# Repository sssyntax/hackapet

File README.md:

# Hackapet

A YSWS where you code + design a virtual pet, and we ship you a physical hackable tamagotchi clone to play it on!

Check out the site: https://hackapet.hackclub.com - includes more info + getting started guide!

## on submissions

When you've finished your game, create a PR in the /pets folder! 

Call your PR whatever your pet/game is named - also, **put your slack username in the PR comment so I can find you**!!

Note:
- you must be in high school (or younger!)
- all art must be drawn by you
- try to have at least 2 minutes of gameplay
- also: try to add on something more than what the example has

This YSWS ends Fed 3rd - get your pets in before then :D

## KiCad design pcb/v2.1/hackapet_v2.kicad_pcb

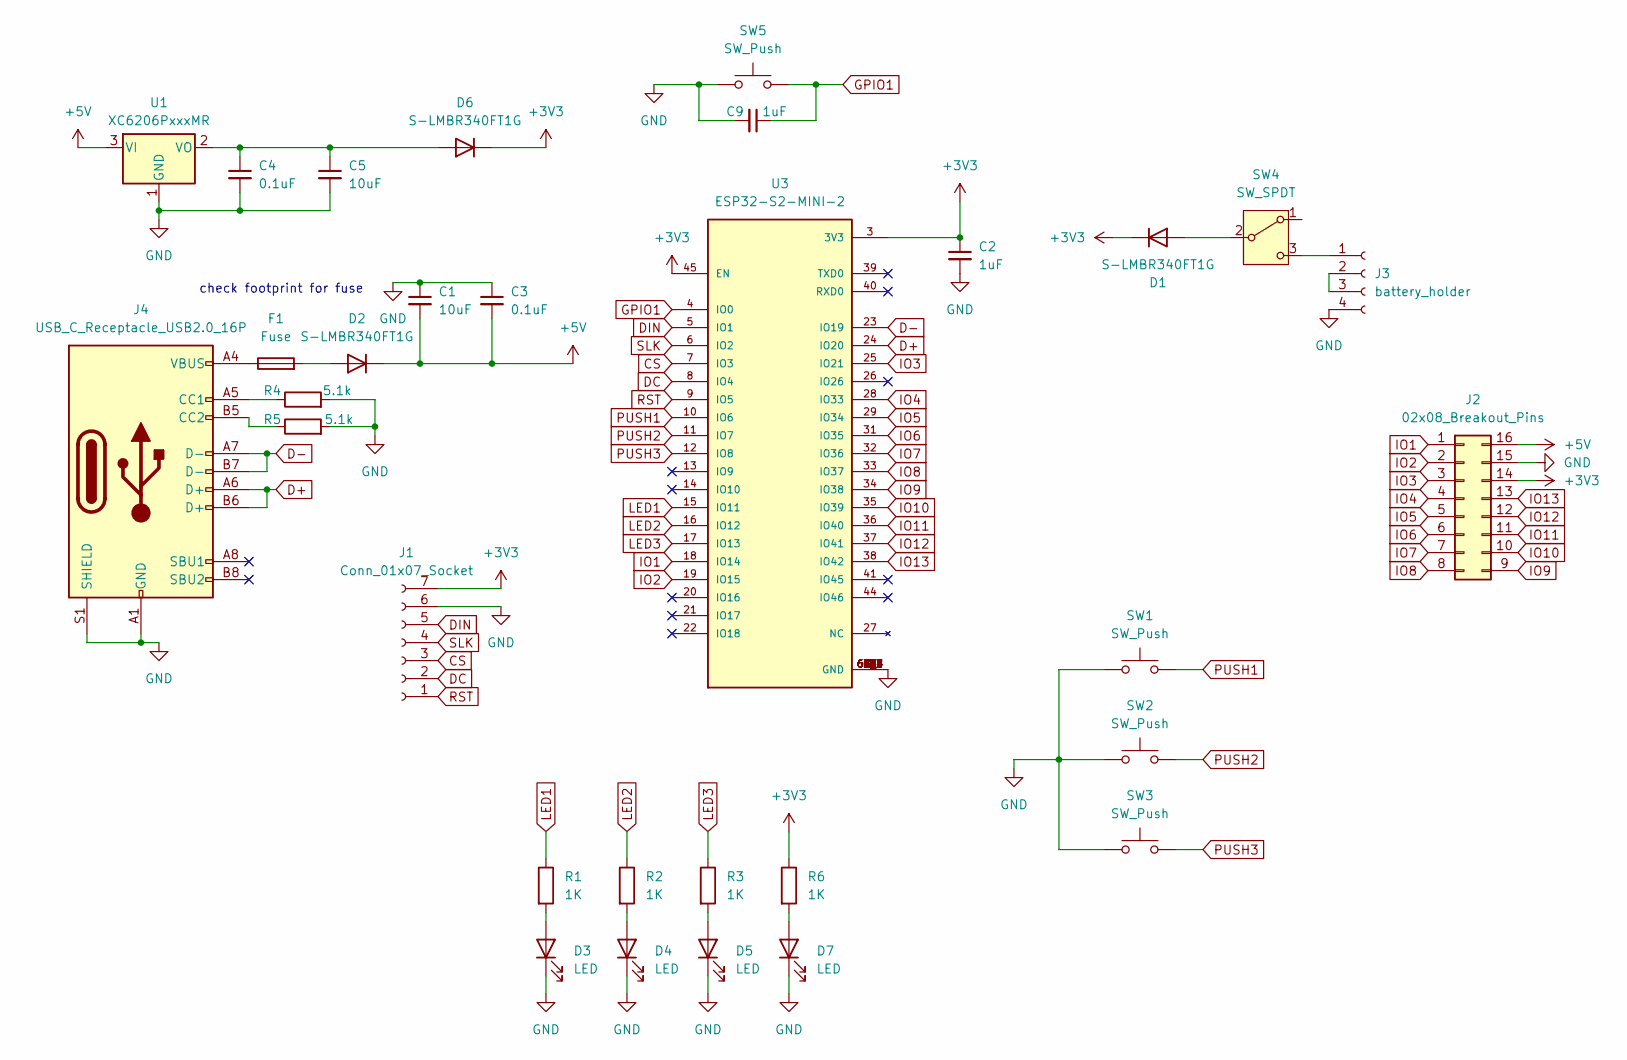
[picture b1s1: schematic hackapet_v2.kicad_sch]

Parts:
C1, C5: 10uF; C_0805_2012Metric; LCSC C5189822
C2, C9: 1uF; C_0805_2012Metric; LCSC C215803
C3, C4: 0.1uF; C_0805_2012Metric; LCSC C28378
D1, D2, D6: S-LMBR340FT1G; D_0805_2012Metric; LCSC C2972823
D3, D4, D5, D7: LED; LED_0805_2012Metric
F1: Fuse; Fuse_Bourns_MF-RHT050
J1: Conn_01x07_Socket; PinSocket_1x07_P2.54mm_Vertical; LCSC C22438073
J2: 02x08_Breakout_Pins; PinSocket_2x08_P2.54mm_Vertical; LCSC C30734
J3: battery_holder; 1022_batteryholder
J4: USB_C_Receptacle_USB2.0_16P; USB_C_Receptacle_HCTL_HC-TYPE-C-16P-01A; LCSC C393939
R1, R2, R3, R6: 1K; R_0805_2012Metric; LCSC C17513
R4, R5: 5.1k; R_0805_2012Metric; LCSC C104375
SW1, SW2, SW3, SW5: SW_Push; SW_Push_1P1T_NO_6x6mm_H9.5mm; LCSC C381038
SW4: SW_SPDT; SW_DPDT_CK_JS202011JCQN; LCSC C221666
U1: XC6206PxxxMR; SOT-23-3
U3: ESP32-S2-MINI-2; XCVR_ESP32-S2-MINI-1; PARTREV 1.0; LCSC C3013906

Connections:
+3V3: C2.1, D1.1 (K), D6.1 (K), J1.7, J2.14, R6.1, U3.3 (3V3), U3.45 (EN)
+5V: C1.2, C3.2, D2.1 (K), J2.16, U1.3 (VI)
CS: J1.3, U3.7 (IO3)
D+: J4.A6 (D+), J4.B6 (D+), U3.24 (IO20)
D-: J4.A7 (D-), J4.B7 (D-), U3.23 (IO19)
DC: J1.2, U3.8 (IO4)
DIN: J1.5, U3.5 (IO1)
GND: C1.1, C2.2, C3.1, C4.2, C5.2, C9.2, D3.1 (K), D4.1 (K), D5.1 (K), D7.1 (K), J1.6, J2.15, J3.4, J4.A1 (GND), J4.A12 (GND), J4.B1 (GND), J4.B12 (GND), J4.S1 (SHIELD), R4.2, R5.2, SW1.1, SW2.1, SW3.1, SW5.1, U1.1 (GND), U3.1 (GND), U3.2 (GND), U3.30 (GND), U3.42 (GND), U3.43 (GND), U3.46 (GND), U3.47 (GND), U3.48 (GND), U3.49 (GND), U3.50 (GND), U3.51 (GND), U3.52 (GND), U3.53 (GND), U3.54 (GND), U3.55 (GND), U3.56 (GND), U3.57 (GND), U3.58 (GND), U3.59 (GND), U3.60 (GND), U3.61 (GND), U3.61_1 (GND), U3.61_2 (GND), U3.61_3 (GND), U3.61_4 (GND), U3.61_5 (GND), U3.61_6 (GND), U3.61_7 (GND), U3.61_8 (GND), U3.62 (GND), U3.63 (GND), U3.64 (GND), U3.65 (GND)
GPIO1: C9.1, SW5.2, U3.4 (IO0)
IO1: J2.1, U3.18 (IO14)
IO2: J2.2, U3.19 (IO15)
IO3: J2.3, U3.25 (IO21)
IO4: J2.4, U3.28 (IO33)
IO5: J2.5, U3.29 (IO34)
IO6: J2.6, U3.31 (IO35)
IO7: J2.7, U3.32 (IO36)
IO8: J2.8, U3.33 (IO37)
IO9: J2.9, U3.34 (IO38)
IO10: J2.10, U3.35 (IO39)
IO11: J2.11, U3.36 (IO40)
IO12: J2.12, U3.37 (IO41)
IO13: J2.13, U3.38 (IO42)
LED1: R1.1, U3.15 (IO11)
LED2: R2.1, U3.16 (IO12)
LED3: R3.1, U3.17 (IO13)
unnamed: D1.2 (A), SW4.2 (B)
unnamed: D2.2 (A), F1.2
unnamed: D3.2 (A), R1.2
unnamed: D4.2 (A), R2.2
unnamed: D5.2 (A), R3.2
unnamed: C4.1, C5.1, D6.2 (A), U1.2 (VO)
unnamed: D7.2 (A), R6.2
unnamed: F1.1, J4.A4 (VBUS), J4.A9 (VBUS), J4.B4 (VBUS), J4.B9 (VBUS)
unnamed: J3.1, SW4.3 (C)
unnamed: J3.2, J3.3
unnamed: J4.A5 (CC1), R4.1
unnamed: J4.B5 (CC2), R5.1
PUSH1: SW1.2, U3.10 (IO6)
PUSH2: SW2.2, U3.11 (IO7)
PUSH3: SW3.2, U3.12 (IO8)
RST: J1.1, U3.9 (IO5)
SLK: J1.4, U3.6 (IO2)

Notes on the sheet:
check footprint for fuse

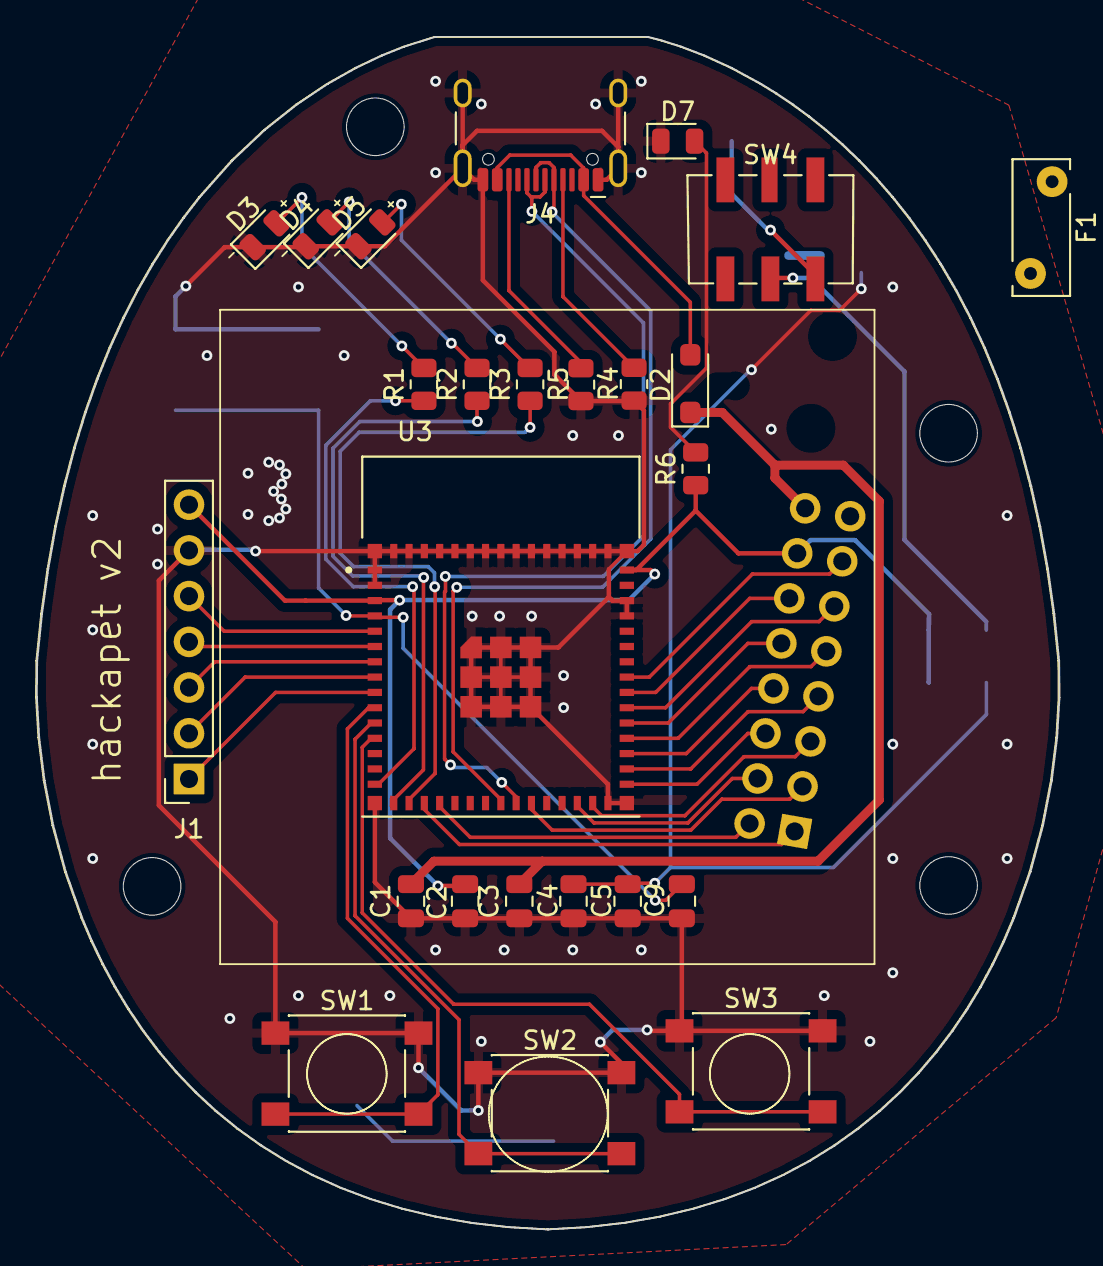
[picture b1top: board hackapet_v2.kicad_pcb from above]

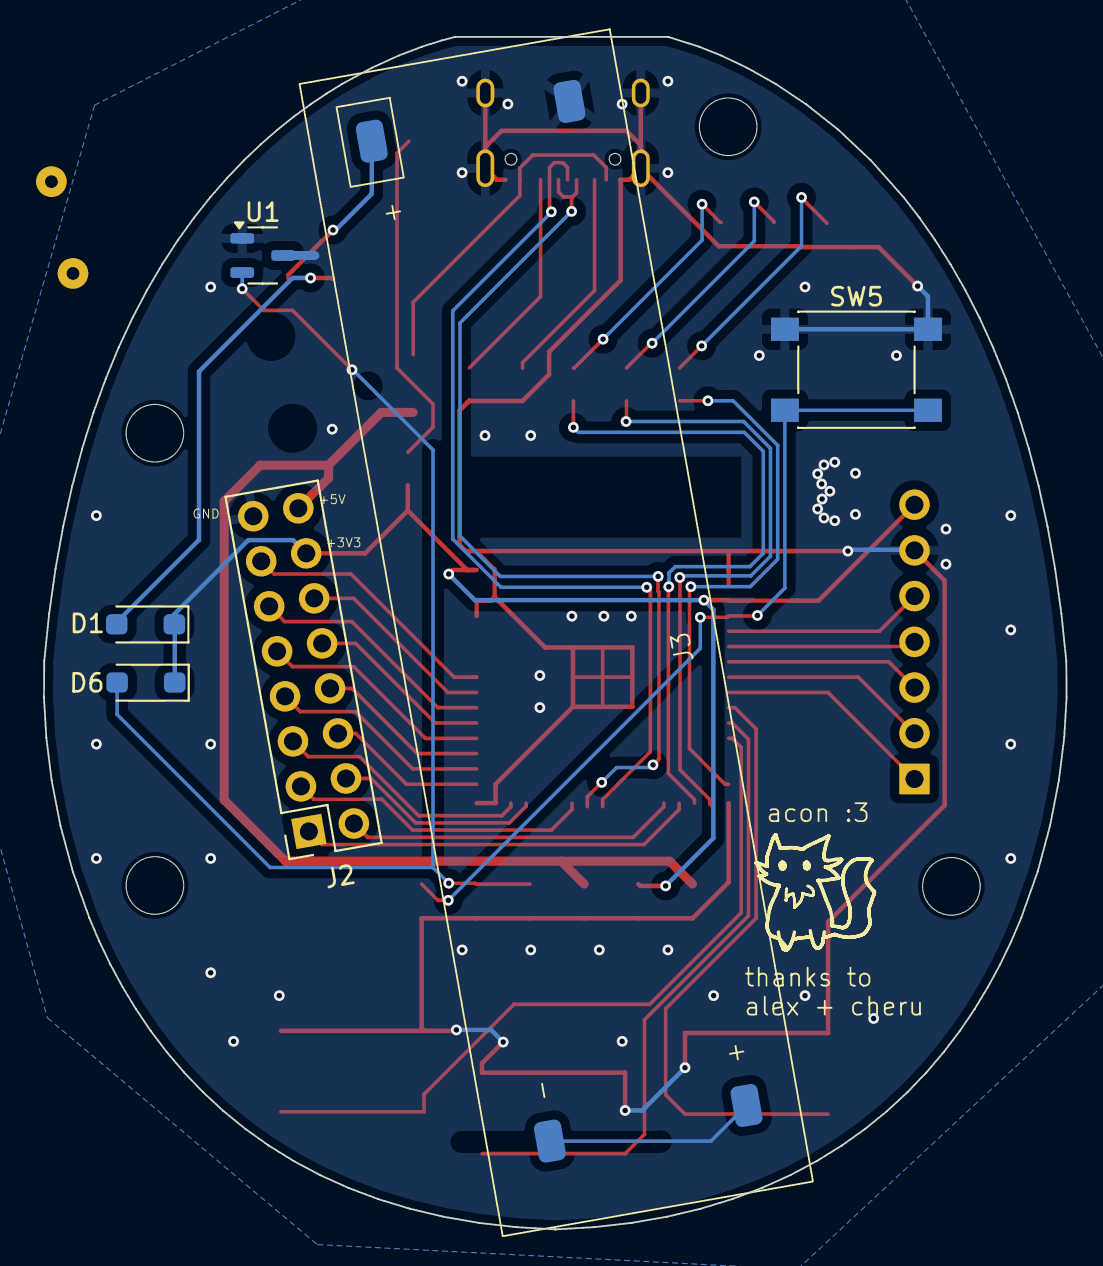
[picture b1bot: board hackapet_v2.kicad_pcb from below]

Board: 2 copper layers, 56.8 x 66.2 mm, 31 parts (6 on the bottom side), 42 nets.

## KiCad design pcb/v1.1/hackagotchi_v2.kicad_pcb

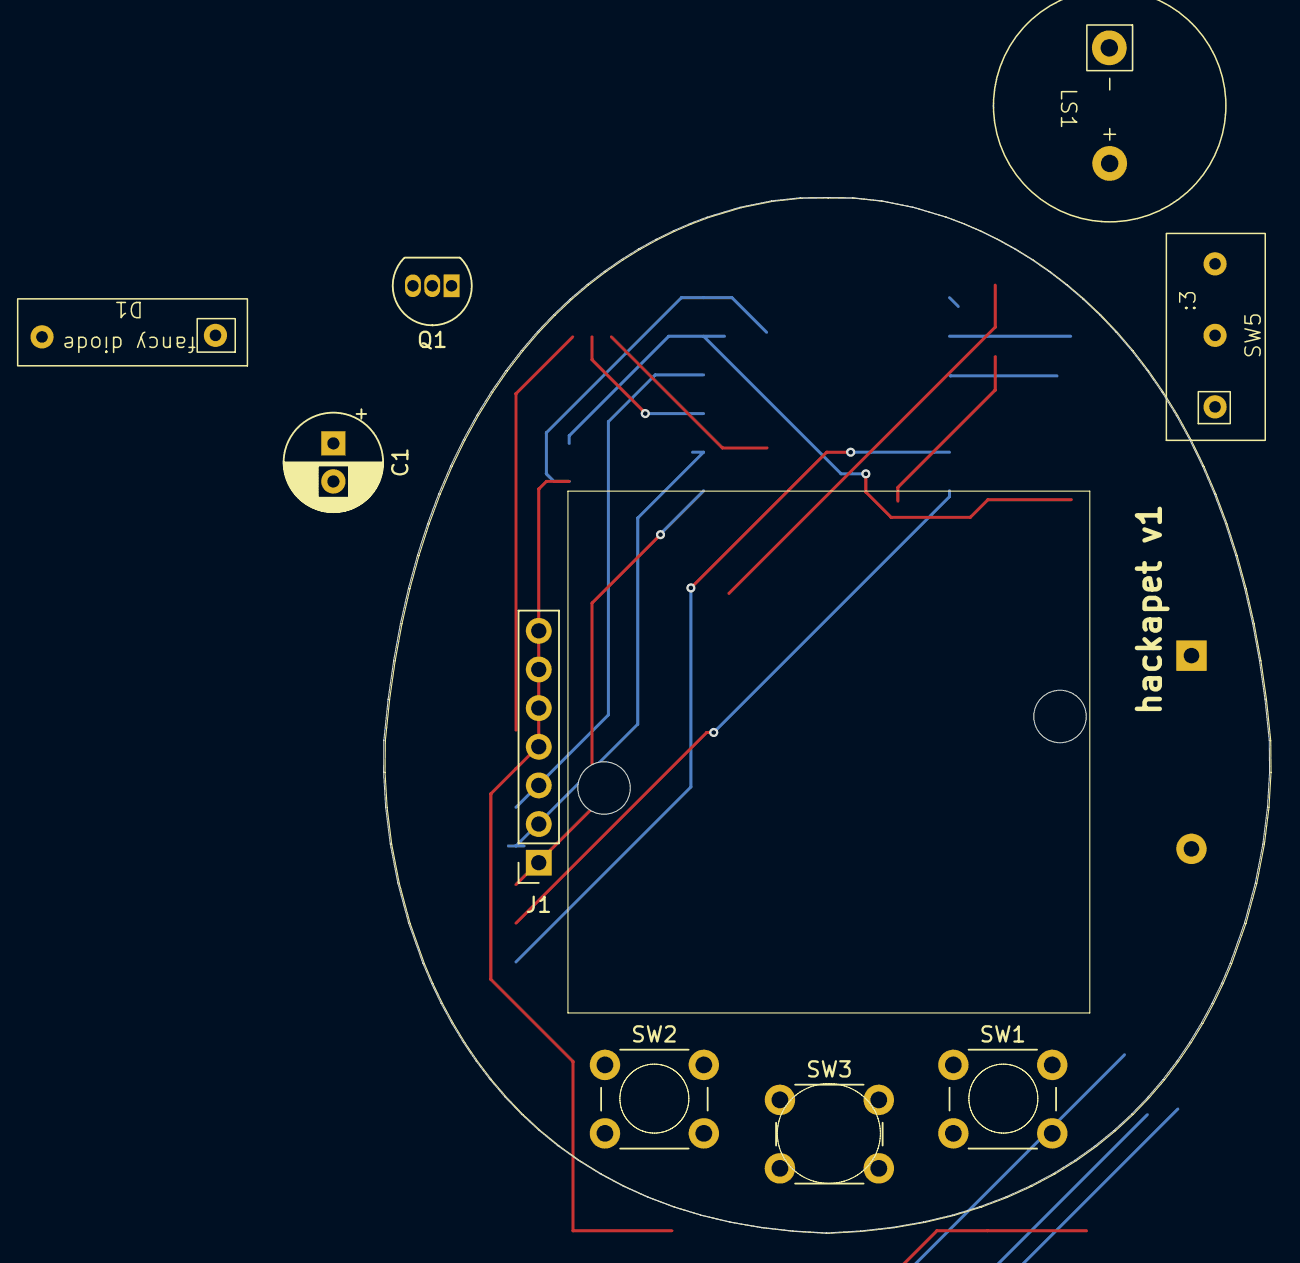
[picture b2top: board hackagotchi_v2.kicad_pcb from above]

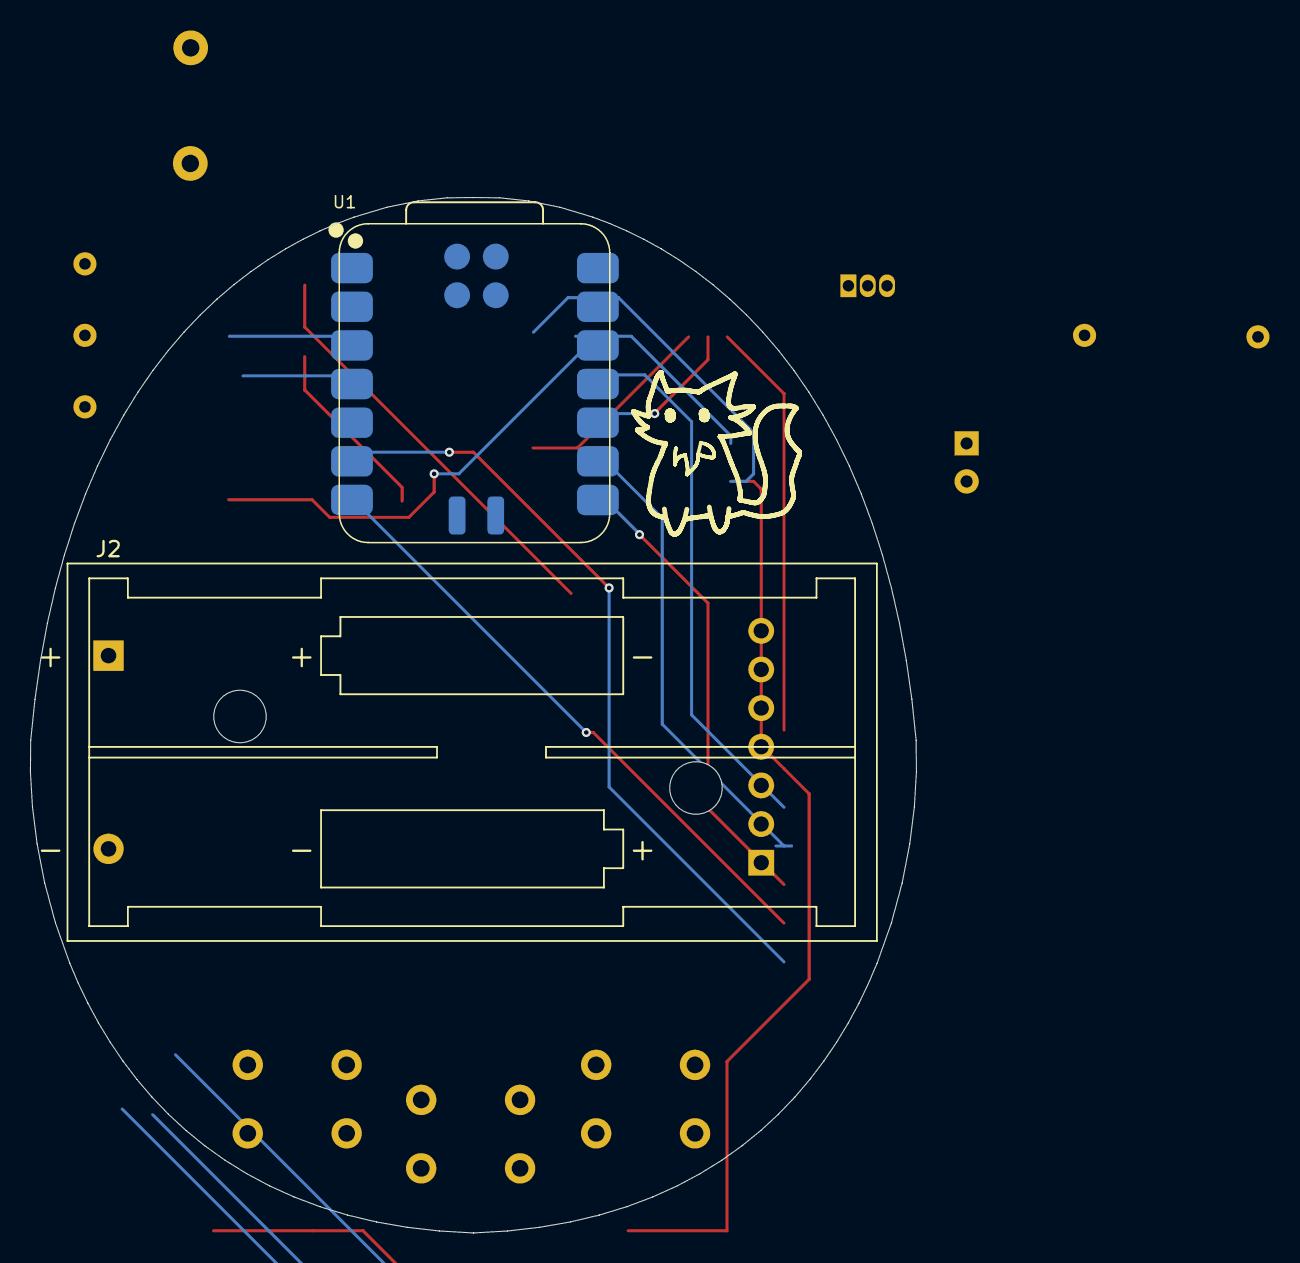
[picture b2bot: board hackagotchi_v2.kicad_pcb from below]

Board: 2 copper layers, 11 parts (2 on the bottom side), 16 nets.

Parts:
C1: 1uF; CP_Radial_D6.3mm_P2.50mm
D1: D_Schottky; 1N5817_amazondiode2
J1: Conn_01x07_Socket; PinSocket_1x07_P2.54mm_Vertical
J2: battery_holder; BatteryHolder_Keystone_2468_2xAAA
LS1: Speaker; CVS_1508custom
Q1: BC557; TO-92_Inline
SW1, SW2, SW3: SW_Push; SW_PUSH_6mm
SW5: SW_SPDT; SPDT-amazonl0lz
U1: Seeed Studio XIAO SAMD21; XIAO-RP2040-SMD

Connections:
+3.3V: J1.7, Q1.3 (E)
CS: J1.3, U1.8 (PB09_A7_D7_RX)
DC: J1.2, U1.7 (PB08_A6_D6_TX)
DIN: J1.5, U1.11 (PA6_A10_D10_MOSI)
GND: C1.2, J1.6, LS1.1, SW2.1, U1.13 (GND)
unnamed: D1.2 (A), SW5.2 (B)
unnamed: C1.1, D1.1 (K), U1.12 (3V3)
unnamed: J2.1, SW5.3 (C)
unnamed: LS1.2, Q1.1 (C)
unnamed: SW1.1, SW3.1
unnamed: SW1.2, U1.2 (PA4_A1_D1)
unnamed: SW2.2, U1.3 (PA10_A2_D2)
unnamed: SW3.2, U1.4 (PA11_A3_D3)
RST: J1.1, U1.6 (PA9_A5_D5_SCL)
SLK: J1.4, U1.9 (PA7_A8_D8_SCK)
SPEAKER: Q1.2 (B), U1.10 (PA5_A9_D9_MISO)

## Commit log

2024-11-27 initial commit, added v1 + v2 pcb files and made README - this @qcoral on acon's pc l0lz
2024-12-13 moved v2 to 1.1, added new versions
2024-12-13 added vite template
2024-12-13 change hero
2024-12-13 added footer
2024-12-13 update footer text
2024-12-14 styling + added section
2024-12-16 update subheading steps text
2024-12-16 added "whats in the box" section
2024-12-16 update favicon
2024-12-16 fix typo
2024-12-16 add watercolor ish background
2024-12-16 copy edit
2024-12-18 add games folder
2024-12-24 update buttons to reflect unclickable status
2024-12-24 add margins
2024-12-26 credit
2024-12-26 alex is picky abt names
2024-12-26 im so extra ab names
2025-01-02 add bobble
2025-01-02 added pictures to site
2025-01-03 added test scripts
2025-01-03 edited folder name on site
2025-01-03 upload apet example
2025-01-03 update cat bmp to png to show up on firefox browser
2025-01-03 add link to /pets folder
2025-01-04 fix typo :skull:
2025-01-06 update game
2025-01-06 updated landing
2025-01-07 add fireball + restart icon sprites
2025-01-08 add some text
2025-01-08 install react router
2025-01-09 added warning for non-mac/linux users, added missing dependency for setup
2025-01-09 attempt
2025-01-09 breaking it
2025-01-09 added page routing, tailwindcss prose, mdx support
2025-01-10 changed sans-serifs to neuebit, added link for #hackapet
2025-01-11 added and finished chess
2025-01-11 removed unneccesary .png file
2025-01-17 this is for alex
2025-01-17 added email button
2025-01-17 add analytics
2025-01-17 moved api route
2025-01-17 ??? LOL
2025-01-17 ?? lol2
2025-01-17 added verceljson for redirects
2025-01-17 styling changes
2025-01-17 added toolbar from hackpad
2025-01-17 Fix missing word
2025-01-19 Add MinePet
2025-01-19 Add README for MinePet
2025-01-19 Add Rock Paper Scissors
2025-01-19 Adding dracula's pet!!
2025-01-21 change email color
2025-01-21 wording change
2025-01-21 update submission criteria text
2025-01-21 copy edits
2025-01-21 add poppins font
2025-01-21 restructured pets, added env setup page
2025-01-21 fixed toolbar
2025-01-21 update guide
2025-01-21 guide copy changes
2025-01-21 Made my own fireball!
2025-01-21 add art + art resources
2025-01-21 copy update
2025-01-21 Add requirements.txt and coord hud in noclip mode
2025-01-22 Added Balloon Cat
2025-01-22 -r'd in EnvSetup.mdx
2025-01-23 added support for bmp and make it use the libraries specified for the project
2025-01-24 Fix guide typos
2025-01-24 Added the ability to replay, and changed the background!
2025-01-24 Adding my little crab! and have organized the code.....
2025-01-24 Editing restart background, adding wings when the dog flies, and the game freezes when you touch the crab.
2025-01-24 Update README, add requirements, check for server
2025-01-24 Replaced the down button with a combination of left and right buttons.
2025-01-25 Game Uploaded
2025-01-25 Added Hackamon
2025-01-25 Added game files
2025-01-26 Create keep
2025-01-26 added assets
2025-01-26 added fonts
2025-01-26 start stuff
2025-01-27 bg + end redrawn, highscore added
2025-01-27 text change
2025-01-27 font added
2025-01-27 typo
2025-01-28 Add more features
2025-01-28 MVP i guess
2025-01-28 feat: add glorbus
2025-01-28 feat: glorbus -> gurgle
2025-01-29 So, here's the first attempt
2025-01-29 feat: pizza! and updated textures and ufo animation
2025-01-29 Fixed backround switching and fixed text
2025-01-29 Fixing wings at the ground
2025-01-29 Added my sad excuse of a rhythm game
2025-01-29 Adding wing animations!
2025-01-29 feat: new art!
2025-01-29 fix: hide_text working
2025-01-29 added my train pet
2025-01-30 added ContyJet
2025-01-30 Add start screen to Colosion
2025-01-30 Revert "added ContyJet", added in the correct directory nw
2025-01-30 Added Contyjet in a directory
2025-01-30 Added restart text, changed font, only down restarts
2025-01-30 add title screen
2025-01-30 add HP label
2025-01-30 Added game over popup and high score
2025-01-30 Add game over popup sprite
2025-01-30 Update README for MinePet
    to include information about key mappings when running on desktop
2025-01-30 Fix scaling bug
2025-01-30 made the suggested changes
2025-01-30 added a start screen
2025-01-31 Modified method of fonts to be different
    So terminalio module is no longer required, added font from terminalio seperately
2025-01-31 Updated requirements.txt
2025-01-31 Changed fuel, added controls
2025-01-31 Fixed a bug, added a wallpaper for the menu
2025-01-31 Adding 2 more backgrounds
2025-01-31 Create GooseOdyssey
2025-01-31 Revert "Create GooseOdyssey"
    This reverts commit ad6cb70f8350aff4527069167d69e87bb3917e6d.
2025-01-31 did it work this time
2025-01-31 THERE we go
2025-01-31 Modified pixel arts, added start menu, and changed the overall game mechanism!
2025-01-31 make the game
2025-01-31 cool update
2025-01-31 Fixed animation in IDLE mode, made last gradient slightly darker
2025-02-01 Create how2cat
2025-02-01 added how2cat
2025-02-13 made changes to code and readme
